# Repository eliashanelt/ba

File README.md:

# Bachelor Thesis: Enhancing the Self-Excited FluidFM Cantilever System
This is the official repo of my bachelor thesis. I will be working on improving LBB's self-excited FluidFM cantilever system
#### Where to find me?
_ETZ E 60.1_

#### Important Links
[nas setup](https://wiki.lbb.ethz.ch/it/backup)

[lbb wiki](https://people.ee.ethz.ch/~lbbwiki/doku.php?id=start)

#### How to flash fpga
open firmware/fpga/tmp/freq/freq.xpr with vivado
generate bitstream file with 'Generate Bitstream'

in firmware/fpga/tmp/freq/freq.runs/impl_1 create system_wrapper.bif containing:
all: { system_wrapper.bit }

also navigate there with the tcl shell and run
bootgen -image system_wrapper.bif -arch zynq -process_bitstream bin -o system_wrapper.bit.bin -w

after that run with the normal shell in that folder:
scp system_wrapper.bit.bin root@rp-f0bbb6.local:/root/

ssh root@rp-f0bbb6.local

password: root

on the redpitaya then run:
fpgautil - b system_wrapper.bit.bin

SCREWS M2 [smartknob] and M3 [redpitaya]

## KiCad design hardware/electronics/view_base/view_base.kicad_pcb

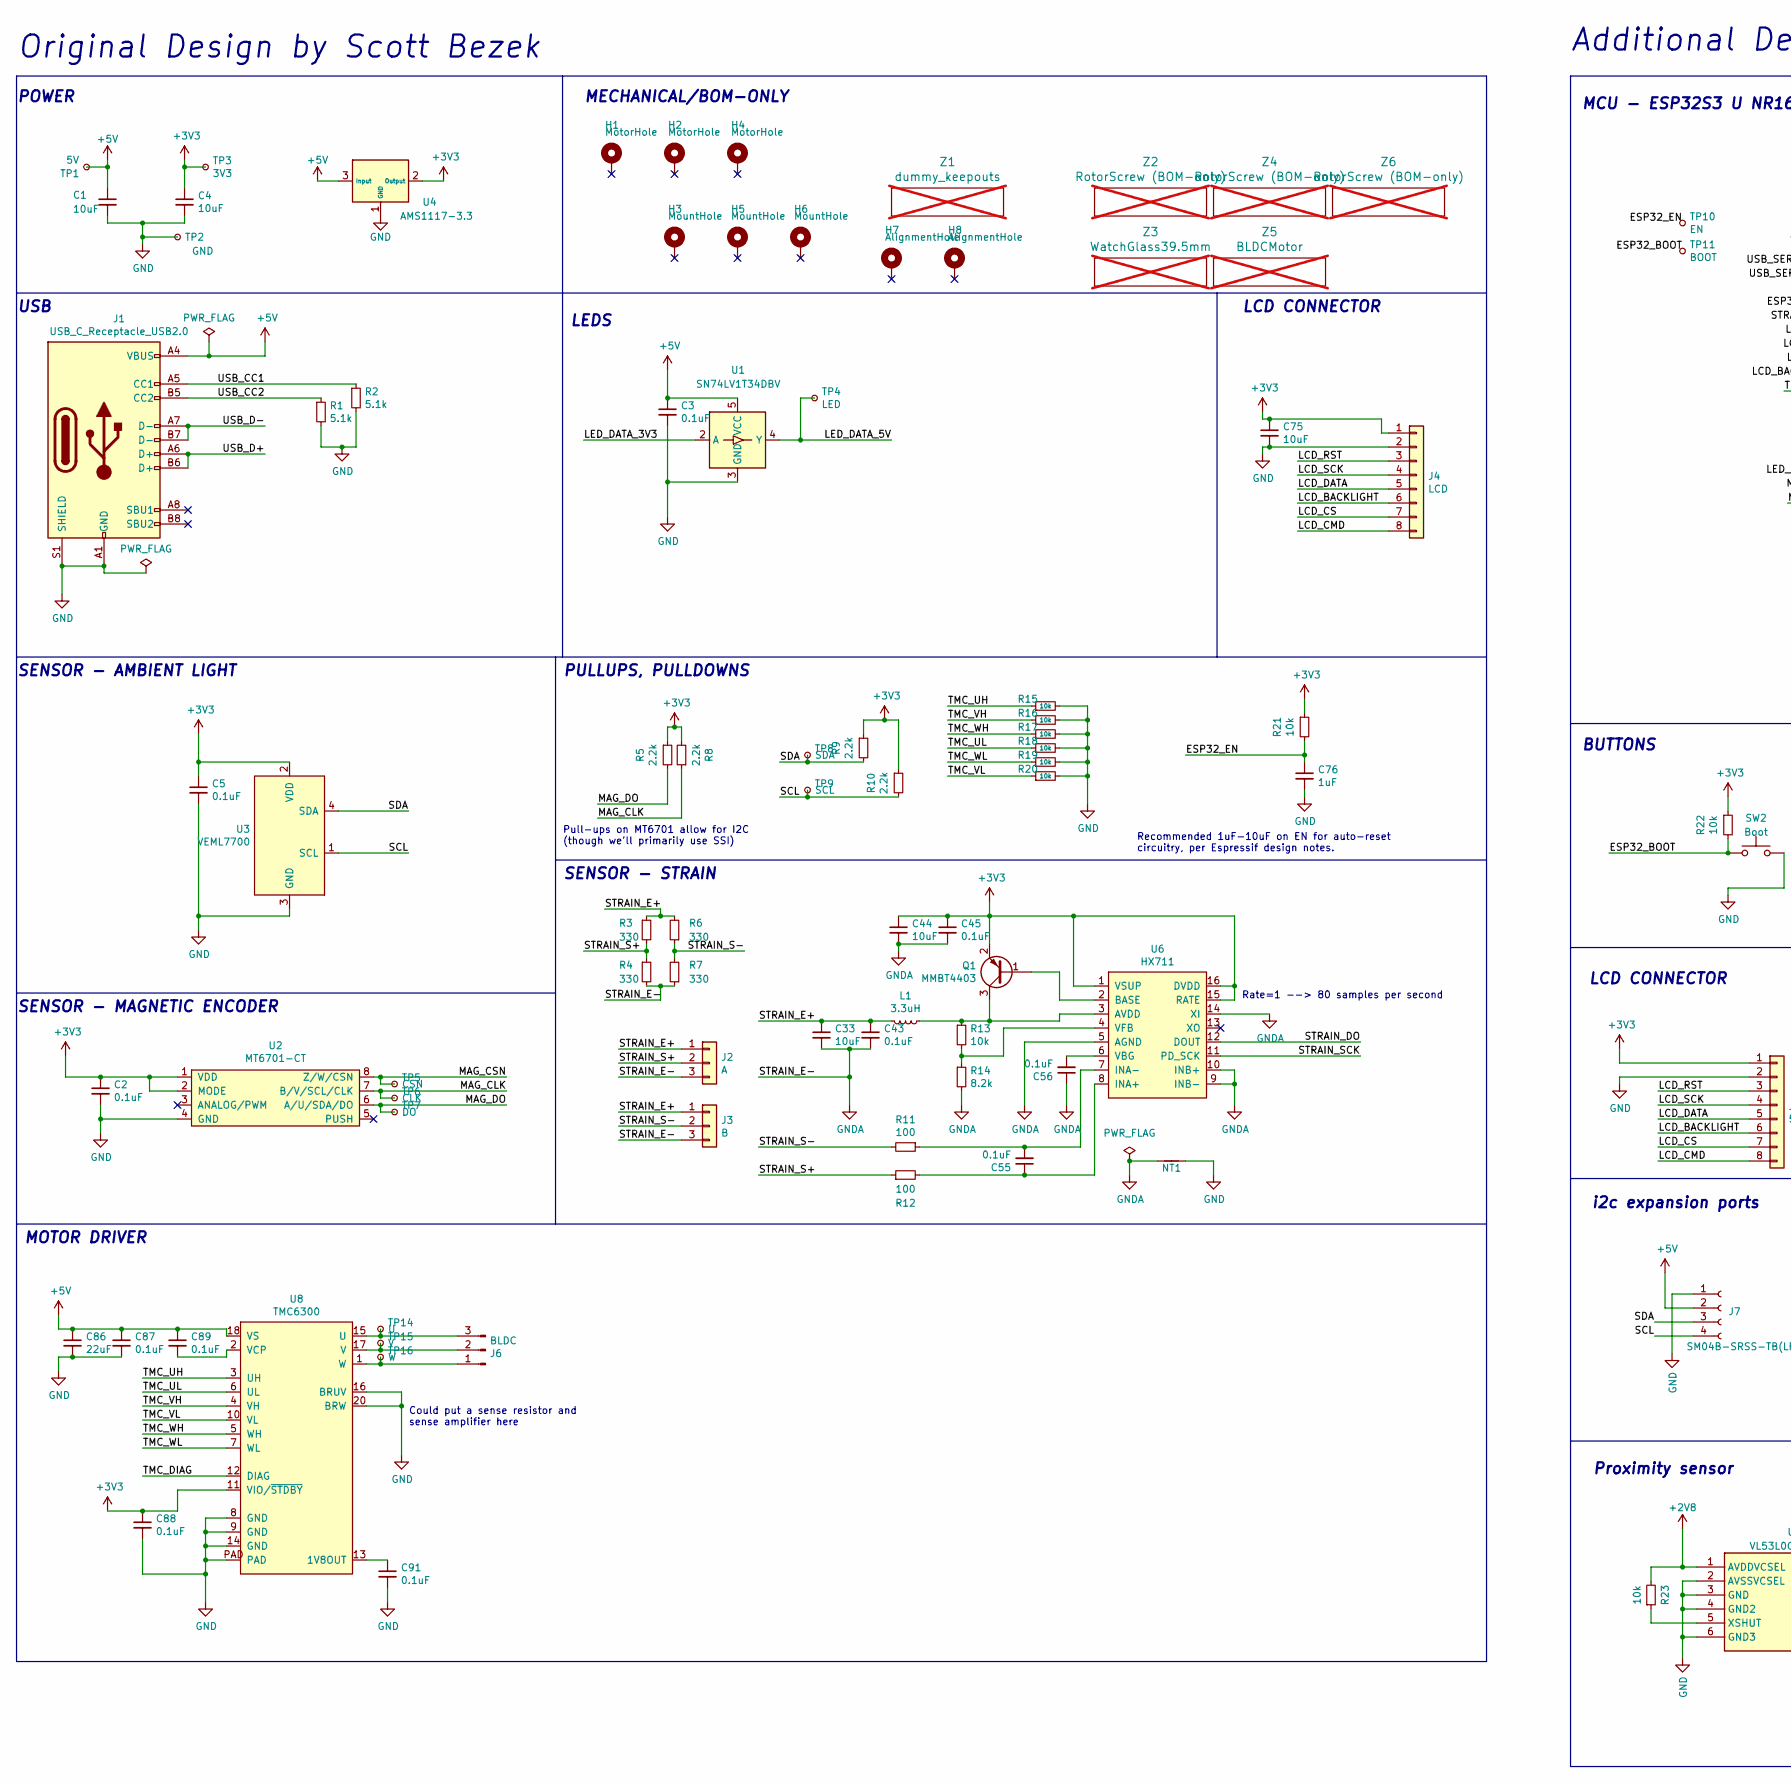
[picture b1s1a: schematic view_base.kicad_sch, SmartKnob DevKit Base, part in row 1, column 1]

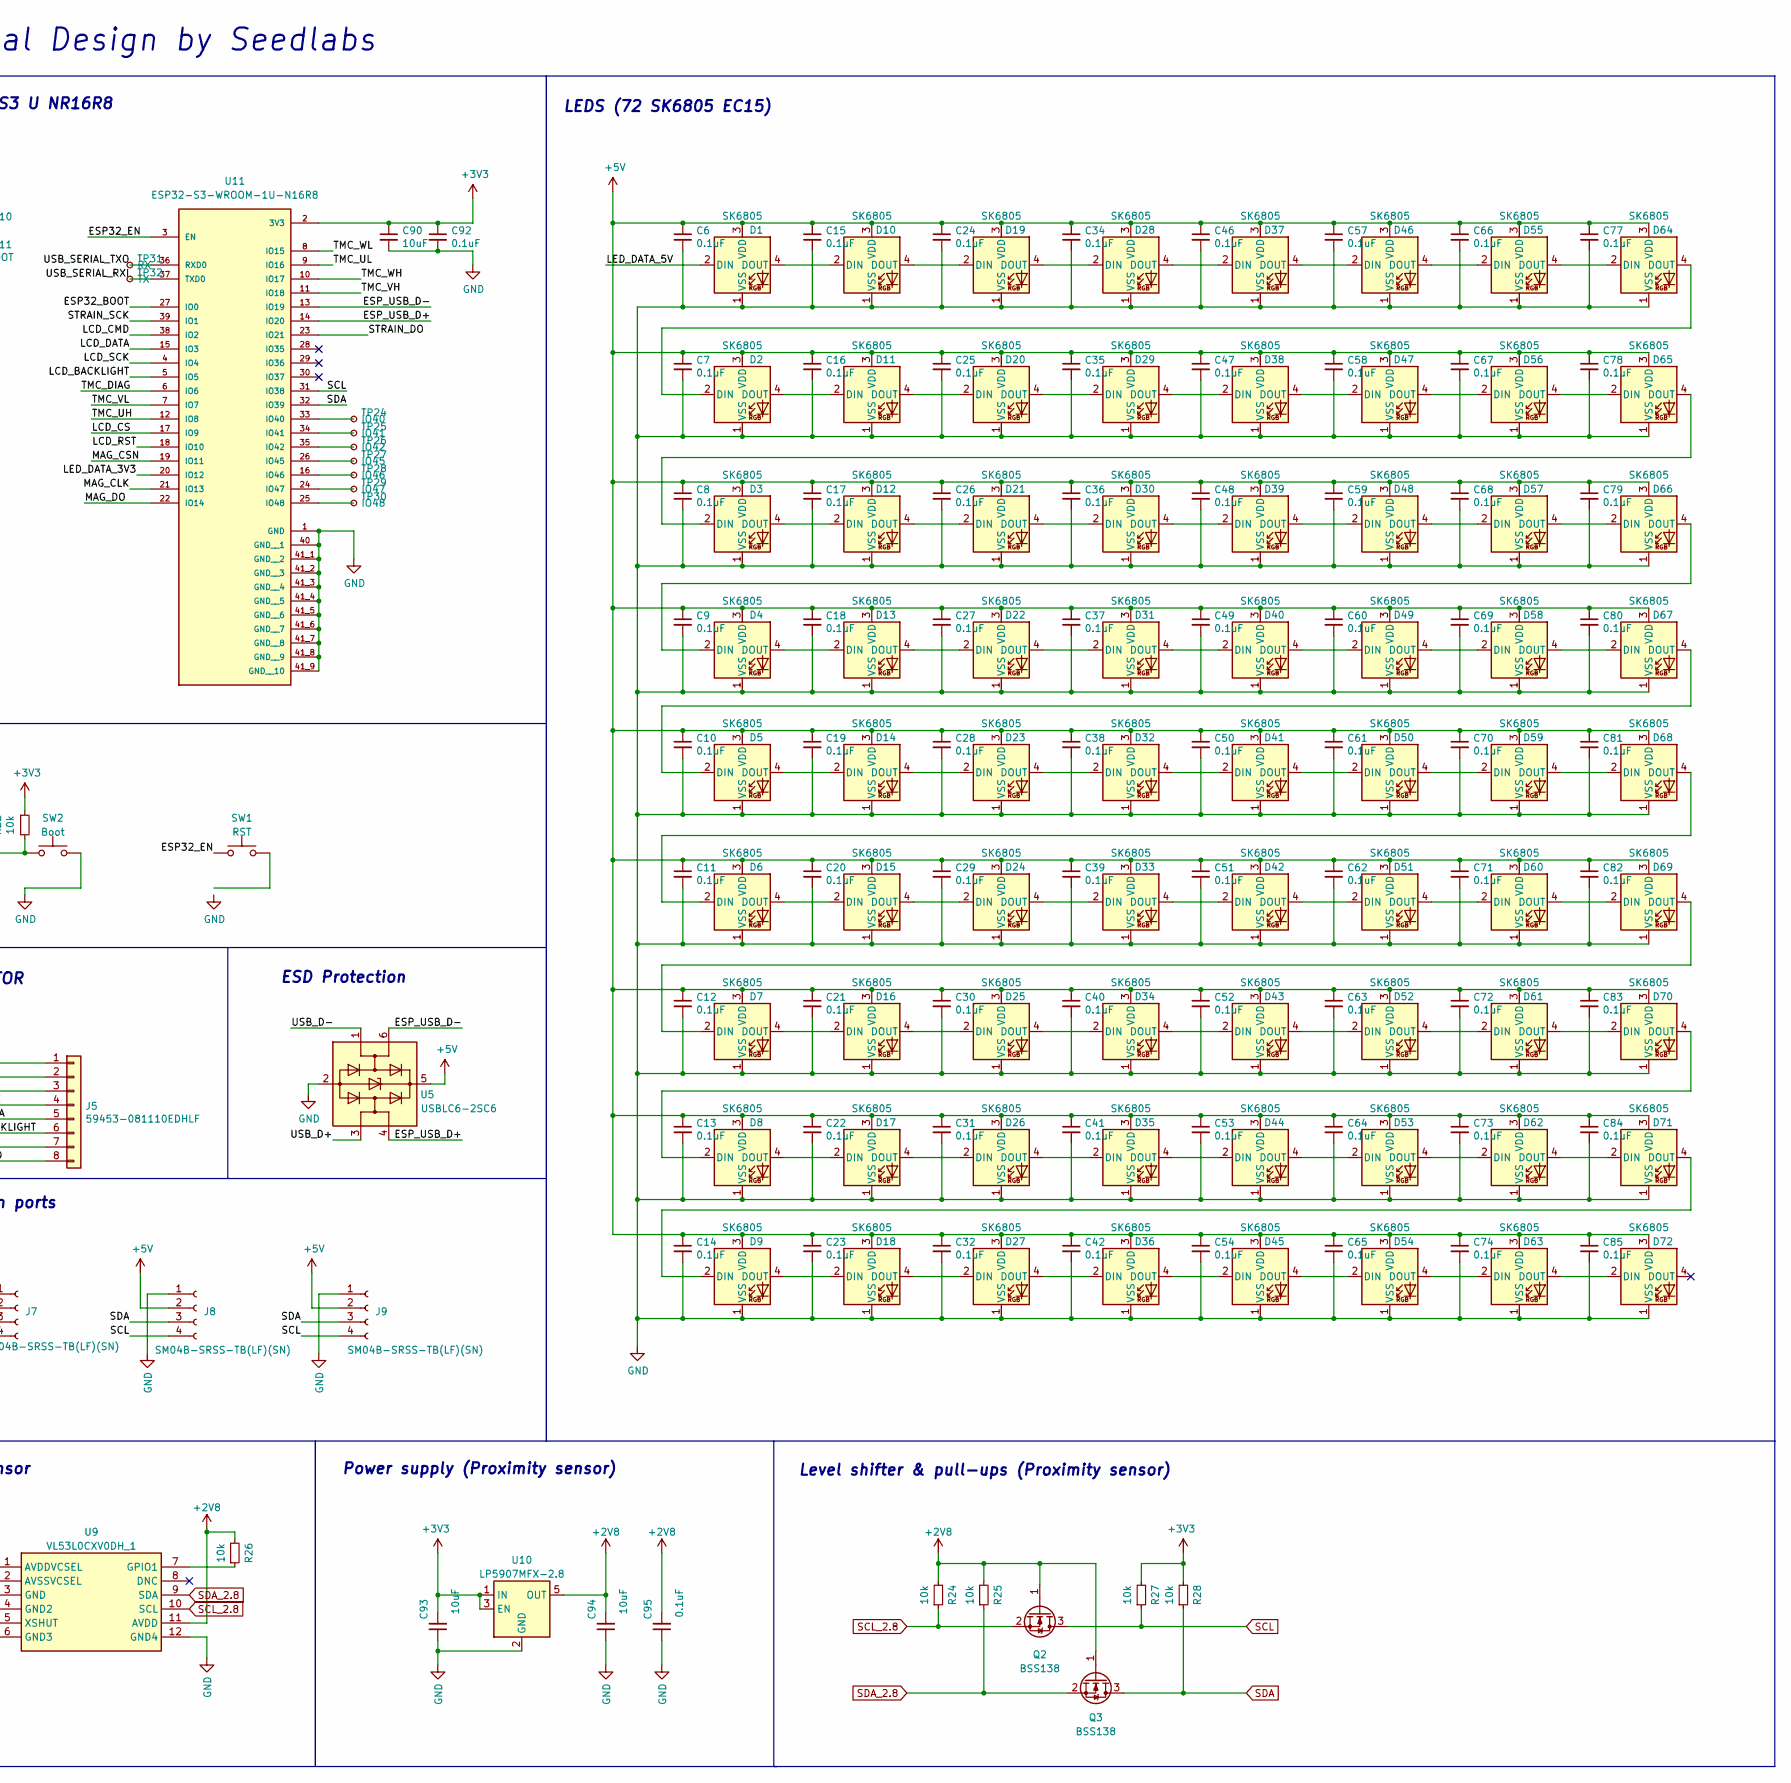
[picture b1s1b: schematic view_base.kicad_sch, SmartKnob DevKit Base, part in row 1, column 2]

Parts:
C1, C4, C33, C44, C75, C90: 10uF; C_0805_2012Metric; LCSC C15850
C2, C3, C5, C43, C45, C55, C56, C87, C88, C89, C91, C92, C95: 0.1uF; C_0603_1608Metric; LCSC C1591
C6, C7, C8, C9, C10, C11, C12, C13, C14, C15, C16, C17, C18, C19, C20, C21, C22, C23, C24, C25, C26, C27, C28, C29, C30, C31, C32, C34, C35, C36, C37, C38, C39, C40, C41, C42, C46, C47, C48, C49, C50, C51, C52, C53, C54, C57, C58, C59, C60, C61, C62, C63, C64, C65, C66, C67, C68, C69, C70, C71, C72, C73, C74, C77, C78, C79, C80, C81, C82, C83, C84, C85: 0.1uF; C_0402_1005Metric; LCSC C83056
C76: 1uF; C_0603_1608Metric; Mouser 187-CL10A105KA8NNNC
C86: 22uF; C_0805_2012Metric; LCSC C98190
C93, C94: 10uF; C_0603_1608Metric; LCSC C38898
D1, D2, D3, D4, D5, D6, D7, D8, D9, D10, D11, D12, D13, D14, D15, D16, D17, D18, D19, D20, D21, D22, D23, D24, D25, D26, D27, D28, D29, D30, D31, D32, D33, D34, D35, D36, D37, D38, D39, D40, D41, D42, D43, D44, D45, D46, D47, D48, D49, D50, D51, D52, D53, D54, D55, D56, D57, D58, D59, D60, D61, D62, D63, D64, D65, D66, D67, D68, D69, D70, D71, D72: SK6805; LED_SK6812_EC15_1.5x1.5mm; LCSC C2890035
H1, H2, H4: MotorHole; MountingHole_M1.6; LCSC C2931389
H3, H5, H6: MountHole; MountingHole_2.2mm_M2_ISO7380_Pad_NonVirtual; LCSC C2911210 or C2911532 (screw), C2961595 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
H7, H8: AlignmentHole; MountingHole_2.2mm_M2_ISO7380_Pad_NonVirtual
J1: USB_C_Receptacle_USB2.0; USB4510_NoPaste; LCSC C428463
J2: A; SolderPads_2mm_3_STRAIN
J3: B; SolderPads_2mm_3_STRAIN
J4: LCD; SolderPads_2mm_8
J5: 59453-081110EDHLF; Amphenol FCI FPC 8 pin 0.5 pitch; Mouser 649-59453081110EDHLF
J6: BLDC; 532610371; LCSC C293630
J7, J8, J9: SM04B-SRSS-TB(LF)(SN); JST_SH_SM04B-SRSS-TB_1x04-1MP_P1.00mm_Horizontal; Mouser 485-4208
L1: 3.3uH; L_0805_2012Metric; LCSC C307744
NT1: NetTie_2; NetTie-2_SMD_Pad0.5mm
Q1: MMBT4403; SOT-23; LCSC C78864
Q2, Q3: BSS138; SOT-23; LCSC C2874697
R1, R2: 5.1k; R_0603_1608Metric; LCSC C105580
R3, R4, R6, R7: 330; R_2512_6332Metric; LCSC C19866
R5, R8, R9, R10: 2.2k; R_0603_1608Metric; LCSC C4190
R11, R12: 100; R_0603_1608Metric; LCSC C319953
R13, R15, R16, R17, R18, R19, R20, R21, R22, R23, R24, R25, R26, R27, R28: 10k; R_0603_1608Metric; LCSC C98220
R14: 8.2k; R_0603_1608Metric; LCSC C114637
SW1: RST; SW_SPST_PTS810; LCSC C116501
SW2: Boot; SW_SPST_PTS810; LCSC C116501
TP1: 5V; TestPoint_Pad_D2.0mm_ValueSilk
TP2: GND; TestPoint_Pad_D2.0mm_ValueSilk
TP3: 3V3; TestPoint_Pad_D2.0mm_ValueSilk
TP4: LED; TestPoint_Pad_D2.0mm_ValueSilk
TP5: CSN; TestPoint_Pad_D2.0mm_ValueSilk
TP6: CLK; TestPoint_Pad_D2.0mm_ValueSilk
TP7: DO; TestPoint_Pad_D2.0mm_ValueSilk
TP8: SDA; TestPoint_Pad_D2.0mm_ValueSilk
TP9: SCL; TestPoint_Pad_D2.0mm_ValueSilk
TP10: EN; TestPoint_Pad_D2.0mm_ValueSilk
TP11: BOOT; TestPoint_Pad_D2.0mm_ValueSilk
TP14: U; TestPoint_Pad_D2.0mm_ValueSilk
TP15: V; TestPoint_Pad_D2.0mm_ValueSilk
TP16: W; TestPoint_Pad_D2.0mm_ValueSilk
TP24: IO40; TestPoint_Pad_D2.0mm_ValueSilk
TP25: IO41; TestPoint_Pad_D2.0mm_ValueSilk
TP26: IO42; TestPoint_Pad_D2.0mm_ValueSilk
TP27: IO45; TestPoint_Pad_D2.0mm_ValueSilk
TP28: IO46; TestPoint_Pad_D2.0mm_ValueSilk
TP29: IO47; TestPoint_Pad_D2.0mm_ValueSilk
TP30: IO48; TestPoint_Pad_D2.0mm_ValueSilk
TP31: RX; TestPoint_Pad_D2.0mm_ValueSilk
TP32: TX; TestPoint_Pad_D2.0mm_ValueSilk
U1: SN74LV1T34DBV; SOT-23-5; LCSC C100024
U2: MT6701-CT; SOIC-8_3.9x4.9mm_P1.27mm; LCSC C2856764, or C3003196
U3: VEML7700; VEML7700-TOP; Digikey VEML7700-TT
U4: AMS1117-3.3; SOT-223-3_TabPin2_GndOutIn; LCSC C6186
U5: USBLC6-2SC6; SOT-23-6; LCSC C7519
U6: HX711; SOIC-16_3.9x9.9mm_P1.27mm; LCSC C43656
U8: TMC6300; QFN-20-1EP_3x3mm_P0.4mm_EP1.65x1.65mm_ThermalVias_LargerVia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; Digikey TMC6300-LA-T
U9: VL53L0CXV0DH_1; LGA12_1; Mouser Part Number 511-VL53L0CXV0DH/1
U10: LP5907MFX-2.8; SOT-23-5; Mouser 595-LP5907MFX-2.8NPB
U11: ESP32-S3-WROOM-1U-N16R8; XCVR_ESP32-S3-WROOM-1U-N16R8; PARTREV v1.1; JLCPCB Position Offset 0,-0.5
Z1: dummy_keepouts; ViewKeepouts3d; not fitted
Z2, Z4, Z6: RotorScrew (BOM-only); bom_only_no_pin; not fitted
Z3: WatchGlass39.5mm; bom_only_no_pin; not fitted
Z5: BLDCMotor; bom_only_no_pin; not fitted

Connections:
+2V8: C94.2, C95.2, Q2.1 (G), Q3.1 (G), R23.2, R24.2, R25.2, R26.2, U9.1 (AVDDVCSEL), U9.11 (AVDD), U10.5 (OUT)
+3V3: C2.1, C4.1, C5.1, C44.1, C45.1, C75.1, C88.1, C90.1, C92.1, C93.2, J4.1, J5.1, Q1.2 (E), R5.1, R8.2, R9.1, R10.1, R21.1, R22.1, R27.2, R28.2, TP3.1, U2.1 (VDD), U2.2 (MODE), U3.2 (VDD), U4.2 (Output), U6.1 (VSUP), U6.15 (RATE), U6.16 (DVDD), U8.11 (VIO/~STDBY), U10.1 (IN), U10.3 (EN), U11.2 (3V3)
+5V: C1.1, C3.1, C6.1, C7.1, C8.1, C9.1, C10.1, C11.1, C12.1, C13.1, C14.1, C15.1, C16.1, C17.1, C18.1, C19.1, C20.1, C21.1, C22.1, C23.1, C24.1, C25.1, C26.1, C27.1, C28.1, C29.1, C30.1, C31.1, C32.1, C34.1, C35.1, C36.1, C37.1, C38.1, C39.1, C40.1, C41.1, C42.1, C46.1, C47.1, C48.1, C49.1, C50.1, C51.1, C52.1, C53.1, C54.1, C57.1, C58.1, C59.1, C60.1, C61.1, C62.1, C63.1, C64.1, C65.1, C66.1, C67.1, C68.1, C69.1, C70.1, C71.1, C72.1, C73.1, C74.1, C77.1, C78.1, C79.1, C80.1, C81.1, C82.1, C83.1, C84.1, C85.1, C86.1, C87.1, C89.1, D1.3 (VDD), D2.3 (VDD), D3.3 (VDD), D4.3 (VDD), D5.3 (VDD), D6.3 (VDD), D7.3 (VDD), D8.3 (VDD), D9.3 (VDD), D10.3 (VDD), D11.3 (VDD), D12.3 (VDD), D13.3 (VDD), D14.3 (VDD), D15.3 (VDD), D16.3 (VDD), D17.3 (VDD), D18.3 (VDD), D19.3 (VDD), D20.3 (VDD), D21.3 (VDD), D22.3 (VDD), D23.3 (VDD), D24.3 (VDD), D25.3 (VDD), D26.3 (VDD), D27.3 (VDD), D28.3 (VDD), D29.3 (VDD), D30.3 (VDD), D31.3 (VDD), D32.3 (VDD), D33.3 (VDD), D34.3 (VDD), D35.3 (VDD), D36.3 (VDD), D37.3 (VDD), D38.3 (VDD), D39.3 (VDD), D40.3 (VDD), D41.3 (VDD), D42.3 (VDD), D43.3 (VDD), D44.3 (VDD), D45.3 (VDD), D46.3 (VDD), D47.3 (VDD), D48.3 (VDD), D49.3 (VDD), D50.3 (VDD), D51.3 (VDD), D52.3 (VDD), D53.3 (VDD), D54.3 (VDD), D55.3 (VDD), D56.3 (VDD), D57.3 (VDD), D58.3 (VDD), D59.3 (VDD), D60.3 (VDD), D61.3 (VDD), D62.3 (VDD), D63.3 (VDD), D64.3 (VDD), D65.3 (VDD), D66.3 (VDD), D67.3 (VDD), D68.3 (VDD), D69.3 (VDD), D70.3 (VDD), D71.3 (VDD), D72.3 (VDD), J1.A4 (VBUS), J1.A9 (VBUS), J1.B4 (VBUS), J1.B9 (VBUS), J7.2, J8.2, J9.2, TP1.1, U1.5 (VCC), U4.3 (Input), U5.5 (VBUS), U8.18 (VS)
/ESP32_BOOT: R22.2, SW2.1, TP11.1, U11.27 (IO0)
/ESP32_EN: C76.1, R21.2, SW1.1, TP10.1, U11.3 (EN)
/ESP_USB_D+: U5.4 (I/O2), U11.14 (IO20)
/ESP_USB_D-: U5.6 (I/O1), U11.13 (IO19)
/LCD_BACKLIGHT: J4.6, J5.6, U11.5 (IO5)
/LCD_CMD: J4.8, J5.8, U11.38 (IO2)
/LCD_CS: J4.7, J5.7, U11.17 (IO9)
/LCD_DATA: J4.5, J5.5, U11.15 (IO3)
/LCD_RST: J4.3, J5.3, U11.18 (IO10)
/LCD_SCK: J4.4, J5.4, U11.4 (IO4)
/LED_DATA_3V3: U1.2 (A), U11.20 (IO12)
/LED_DATA_5V: D1.2 (DIN), TP4.1, U1.4 (Y)
/MAG_CLK: R8.1, TP6.1, U2.7 (B/V/SCL/CLK), U11.21 (IO13)
/MAG_CSN: TP5.1, U2.8 (Z/W/CSN), U11.19 (IO11)
/MAG_DO: R5.2, TP7.1, U2.6 (A/U/SDA/DO), U11.22 (IO14)
/STRAIN_DO: U6.12 (DOUT), U11.23 (IO21)
/STRAIN_E+: C33.1, C43.1, J2.1, J3.1, L1.2, R3.1, R6.2
/STRAIN_S+: J2.2, R3.2, R4.1, R12.1
/STRAIN_S-: J3.2, R6.1, R7.2, R11.2
/STRAIN_SCK: U6.11 (PD_SCK), U11.39 (IO1)
/TMC_DIAG: U8.12 (DIAG), U11.6 (IO6)
/TMC_UH: R15.1, U8.3 (UH), U11.12 (IO8)
/TMC_UL: R18.1, U8.6 (UL), U11.9 (IO16)
/TMC_VH: R16.1, U8.4 (VH), U11.11 (IO18)
/TMC_VL: R20.1, U8.10 (VL), U11.7 (IO7)
/TMC_WH: R17.1, U8.5 (WH), U11.10 (IO17)
/TMC_WL: R19.1, U8.7 (WL), U11.8 (IO15)
/USB_CC1: J1.A5 (CC1), R2.1
/USB_CC2: J1.B5 (CC2), R1.1
/USB_D+: J1.A6 (D+), J1.B6 (D+), U5.3 (I/O2)
/USB_D-: J1.A7 (D-), J1.B7 (D-), U5.1 (I/O1)
/USB_SERIAL_RXI: TP32.1, U11.37 (TXD0); also elsewhere on the board
/USB_SERIAL_TXO: TP31.1, U11.36 (RXD0); also elsewhere on the board
GND: C1.2, C2.2, C3.2, C4.2, C5.2, C6.2, C7.2, C8.2, C9.2, C10.2, C11.2, C12.2, C13.2, C14.2, C15.2, C16.2, C17.2, C18.2, C19.2, C20.2, C21.2, C22.2, C23.2, C24.2, C25.2, C26.2, C27.2, C28.2, C29.2, C30.2, C31.2, C32.2, C34.2, C35.2, C36.2, C37.2, C38.2, C39.2, C40.2, C41.2, C42.2, C46.2, C47.2, C48.2, C49.2, C50.2, C51.2, C52.2, C53.2, C54.2, C57.2, C58.2, C59.2, C60.2, C61.2, C62.2, C63.2, C64.2, C65.2, C66.2, C67.2, C68.2, C69.2, C70.2, C71.2, C72.2, C73.2, C74.2, C75.2, C76.2, C77.2, C78.2, C79.2, C80.2, C81.2, C82.2, C83.2, C84.2, C85.2, C86.2, C87.2, C88.2, C90.2, C91.2, C92.2, C93.1, C94.1, C95.1, D1.1 (VSS), D2.1 (VSS), D3.1 (VSS), D4.1 (VSS), D5.1 (VSS), D6.1 (VSS), D7.1 (VSS), D8.1 (VSS), D9.1 (VSS), D10.1 (VSS), D11.1 (VSS), D12.1 (VSS), D13.1 (VSS), D14.1 (VSS), D15.1 (VSS), D16.1 (VSS), D17.1 (VSS), D18.1 (VSS), D19.1 (VSS), D20.1 (VSS), D21.1 (VSS), D22.1 (VSS), D23.1 (VSS), D24.1 (VSS), D25.1 (VSS), D26.1 (VSS), D27.1 (VSS), D28.1 (VSS), D29.1 (VSS), D30.1 (VSS), D31.1 (VSS), D32.1 (VSS), D33.1 (VSS), D34.1 (VSS), D35.1 (VSS), D36.1 (VSS), D37.1 (VSS), D38.1 (VSS), D39.1 (VSS), D40.1 (VSS), D41.1 (VSS), D42.1 (VSS), D43.1 (VSS), D44.1 (VSS), D45.1 (VSS), D46.1 (VSS), D47.1 (VSS), D48.1 (VSS), D49.1 (VSS), D50.1 (VSS), D51.1 (VSS), D52.1 (VSS), D53.1 (VSS), D54.1 (VSS), D55.1 (VSS), D56.1 (VSS), D57.1 (VSS), D58.1 (VSS), D59.1 (VSS), D60.1 (VSS), D61.1 (VSS), D62.1 (VSS), D63.1 (VSS), D64.1 (VSS), D65.1 (VSS), D66.1 (VSS), D67.1 (VSS), D68.1 (VSS), D69.1 (VSS), D70.1 (VSS), D71.1 (VSS), D72.1 (VSS), J1.A1 (GND), J1.A12 (GND), J1.B1 (GND), J1.B12 (GND), J1.S1 (SHIELD), J4.2, J5.2, J7.1, J8.1, J9.1, NT1.2, R1.2, R2.2, R15.2, R16.2, R17.2, R18.2, R19.2, R20.2, SW1.2, SW2.2, TP2.1, U1.3 (GND), U2.4 (GND), U3.3 (GND), U4.1 (GND), U5.2 (GND), U8.8 (GND), U8.9 (GND), U8.14 (GND), U8.16 (BRUV), U8.20 (BRW), U8.PAD, U9.2 (AVSSVCSEL), U9.3 (GND), U9.4 (GND2), U9.6 (GND3), U9.12 (GND4), U10.2 (GND), U11.1 (GND), U11.40 (GND__1), U11.41_1 (GND__2), U11.41_2 (GND__3), U11.41_3 (GND__4), U11.41_4 (GND__5), U11.41_5 (GND__6), U11.41_6 (GND__7), U11.41_7 (GND__8), U11.41_8 (GND__9), U11.41_9 (GND__10)
GNDA: C33.2, C43.2, C44.2, C45.2, C56.1, J2.3, J3.3, NT1.1, R4.2, R7.1, R14.2, U6.5 (AGND), U6.9 (INB-), U6.10 (INB+), U6.14 (XI)
unnamed: D1.4 (DOUT), D10.2 (DIN)
unnamed: D2.2 (DIN), D64.4 (DOUT)
unnamed: D3.2 (DIN), D65.4 (DOUT)
unnamed: D4.2 (DIN), D66.4 (DOUT)
unnamed: D5.2 (DIN), D67.4 (DOUT)
unnamed: D6.2 (DIN), D68.4 (DOUT)
unnamed: D10.4 (DOUT), D19.2 (DIN)
unnamed: D2.4 (DOUT), D11.2 (DIN)
unnamed: D11.4 (DOUT), D20.2 (DIN)
unnamed: D3.4 (DOUT), D12.2 (DIN)
unnamed: D12.4 (DOUT), D21.2 (DIN)
unnamed: D4.4 (DOUT), D13.2 (DIN)
unnamed: D13.4 (DOUT), D22.2 (DIN)
unnamed: D5.4 (DOUT), D14.2 (DIN)
unnamed: D14.4 (DOUT), D23.2 (DIN)
unnamed: D6.4 (DOUT), D15.2 (DIN)
unnamed: D15.4 (DOUT), D24.2 (DIN)
unnamed: D7.4 (DOUT), D16.2 (DIN)
unnamed: D16.4 (DOUT), D25.2 (DIN)
unnamed: D8.4 (DOUT), D17.2 (DIN)
unnamed: D17.4 (DOUT), D26.2 (DIN)
unnamed: D9.4 (DOUT), D18.2 (DIN)
unnamed: D18.4 (DOUT), D27.2 (DIN)
unnamed: D19.4 (DOUT), D28.2 (DIN)
unnamed: D20.4 (DOUT), D29.2 (DIN)
unnamed: D21.4 (DOUT), D30.2 (DIN)
unnamed: D22.4 (DOUT), D31.2 (DIN)
unnamed: D23.4 (DOUT), D32.2 (DIN)
unnamed: D24.4 (DOUT), D33.2 (DIN)
unnamed: D25.4 (DOUT), D34.2 (DIN)
unnamed: D26.4 (DOUT), D35.2 (DIN)
unnamed: D27.4 (DOUT), D36.2 (DIN)
unnamed: D28.4 (DOUT), D37.2 (DIN)
unnamed: D29.4 (DOUT), D38.2 (DIN)
unnamed: D30.4 (DOUT), D39.2 (DIN)
unnamed: D31.4 (DOUT), D40.2 (DIN)
unnamed: D32.4 (DOUT), D41.2 (DIN)
unnamed: D33.4 (DOUT), D42.2 (DIN)
unnamed: D34.4 (DOUT), D43.2 (DIN)
unnamed: D35.4 (DOUT), D44.2 (DIN)
unnamed: D36.4 (DOUT), D45.2 (DIN)
unnamed: D37.4 (DOUT), D46.2 (DIN)
unnamed: D38.4 (DOUT), D47.2 (DIN)
unnamed: D39.4 (DOUT), D48.2 (DIN)
unnamed: D40.4 (DOUT), D49.2 (DIN)
unnamed: D41.4 (DOUT), D50.2 (DIN)
unnamed: D42.4 (DOUT), D51.2 (DIN)
unnamed: D43.4 (DOUT), D52.2 (DIN)
unnamed: D44.4 (DOUT), D53.2 (DIN)
unnamed: D45.4 (DOUT), D54.2 (DIN)
unnamed: D46.4 (DOUT), D55.2 (DIN)
unnamed: D47.4 (DOUT), D56.2 (DIN)
unnamed: D48.4 (DOUT), D57.2 (DIN)
unnamed: D49.4 (DOUT), D58.2 (DIN)
unnamed: D50.4 (DOUT), D59.2 (DIN)
unnamed: D51.4 (DOUT), D60.2 (DIN)
unnamed: D52.4 (DOUT), D61.2 (DIN)
unnamed: D53.4 (DOUT), D62.2 (DIN)
unnamed: D54.4 (DOUT), D63.2 (DIN)
unnamed: D55.4 (DOUT), D64.2 (DIN)
unnamed: D56.4 (DOUT), D65.2 (DIN)
unnamed: D57.4 (DOUT), D66.2 (DIN)
unnamed: D58.4 (DOUT), D67.2 (DIN)
unnamed: D59.4 (DOUT), D68.2 (DIN)
unnamed: D60.4 (DOUT), D69.2 (DIN)
unnamed: D61.4 (DOUT), D70.2 (DIN)
unnamed: D62.4 (DOUT), D71.2 (DIN)
unnamed: D63.4 (DOUT), D72.2 (DIN)
unnamed: D7.2 (DIN), D69.4 (DOUT)
unnamed: D8.2 (DIN), D70.4 (DOUT)
unnamed: D9.2 (DIN), D71.4 (DOUT)
unnamed: J6.1, TP16.1, U8.1 (W)
unnamed: J6.2, TP15.1, U8.17 (V)
unnamed: J6.3, TP14.1, U8.15 (U)
unnamed: Q1.1 (B), U6.2 (BASE)
unnamed: L1.1, Q1.3 (C), R13.1, U6.3 (AVDD)
unnamed: C55.1, R12.2, U6.8 (INA+)
unnamed: C55.2, R11.1, U6.7 (INA-)
unnamed: C56.2, U6.6 (VBG)
unnamed: R13.2, R14.1, U6.4 (VFB)
unnamed: C91.1, U8.13 (1V8OUT)
unnamed: C89.2, U8.2 (VCP)
unnamed: R26.1, U9.7 (GPIO1)
unnamed: R23.1, U9.5 (XSHUT)
unnamed: TP24.1, U11.33 (IO40)
unnamed: TP25.1, U11.34 (IO41)
unnamed: TP26.1, U11.35 (IO42)
unnamed: TP27.1, U11.26 (IO45)
unnamed: TP28.1, U11.16 (IO46)
unnamed: TP29.1, U11.24 (IO47)
unnamed: TP30.1, U11.25 (IO48)
SCL: J7.4, J8.4, J9.4, Q2.3 (D), R10.2, R27.1, TP9.1, U3.1 (SCL), U11.31 (IO38)
SCL_2.8: Q2.2 (S), R24.1, U9.10 (SCL)
SDA: J7.3, J8.3, J9.3, Q3.3 (D), R9.2, R28.1, TP8.1, U3.4 (SDA), U11.32 (IO39)
SDA_2.8: Q3.2 (S), R25.1, U9.9 (SDA)

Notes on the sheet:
POWER
Could put a sense resistor and sense amplifier here
MCU - ESP32S3 U NR16R8
SENSOR - MAGNETIC ENCODER
MOTOR DRIVER
MECHANICAL/BOM-ONLY
Pull-ups on MT6701 allow for I2C (though we'll primarily use SSI)
Rate=1 --> 80 samples per second
Additional Design by Seedlabs
Proximity sensor
SENSOR - AMBIENT LIGHT
Power supply (Proximity sensor)
Original Design by Scott Bezek
Recommended 1uF-10uF on EN for auto-reset circuitry, per Espressif design notes.
USB
SENSOR - STRAIN
LEDS
LEDS (72 SK6805 EC15)
BUTTONS
PULLUPS, PULLDOWNS
LCD CONNECTOR
i2c expansion ports
ESD Protection
Level shifter & pull-ups (Proximity sensor)

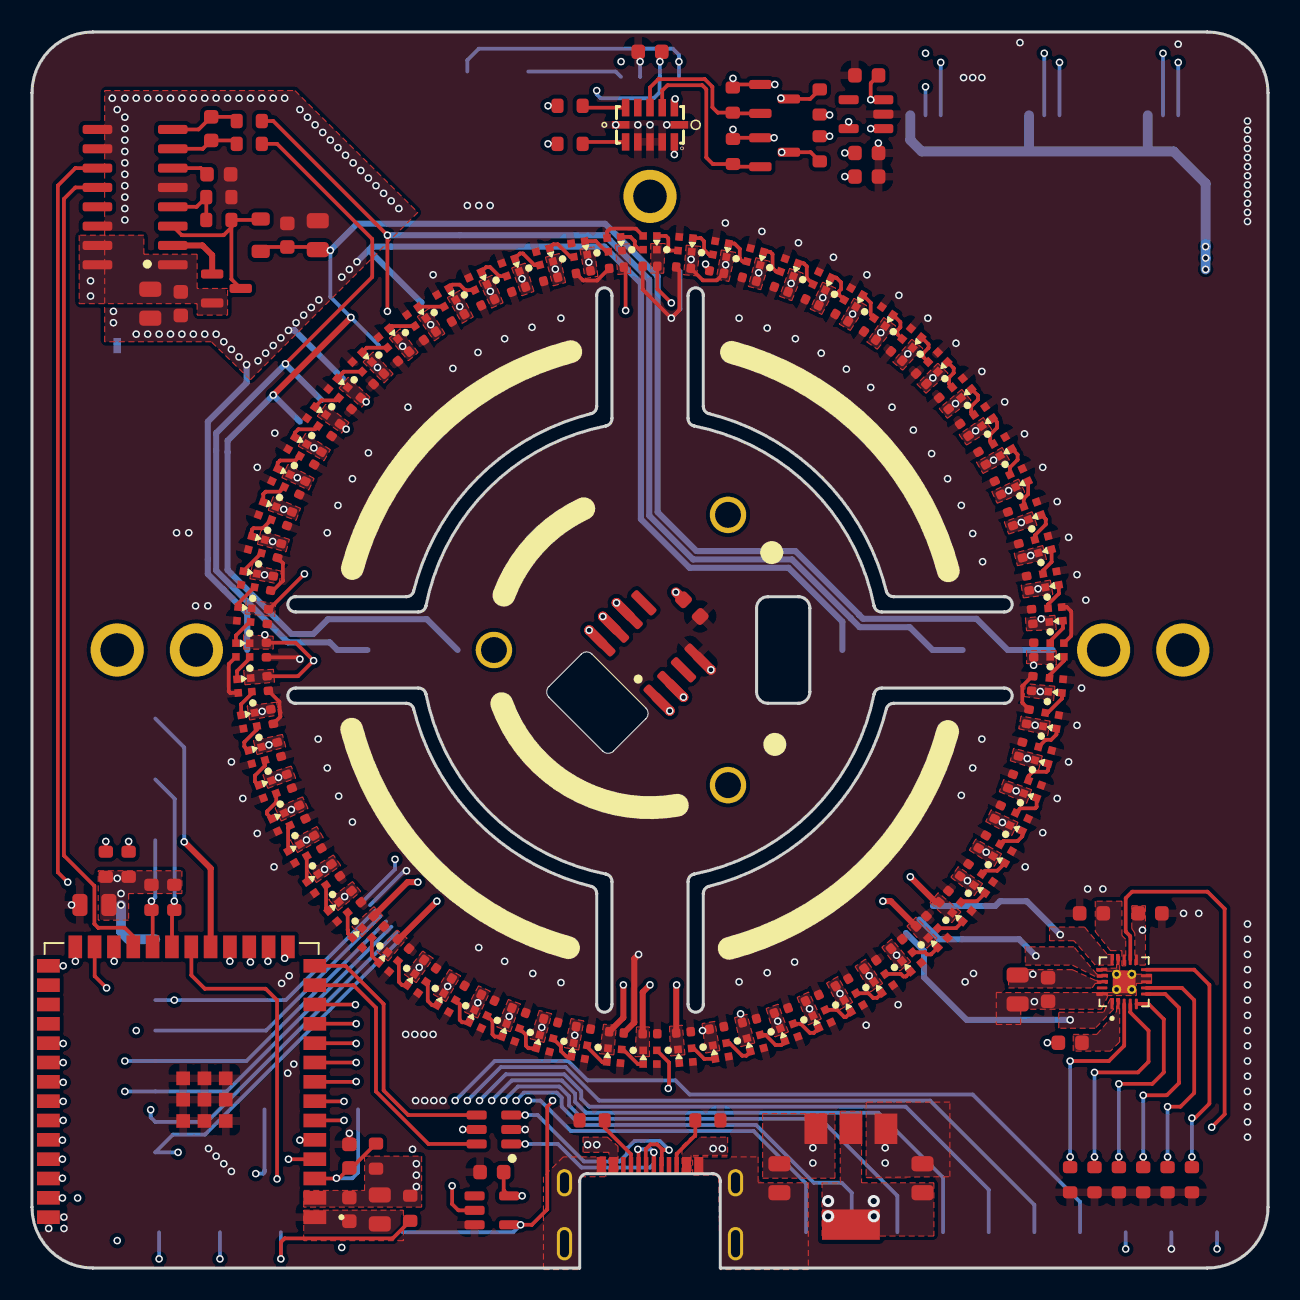
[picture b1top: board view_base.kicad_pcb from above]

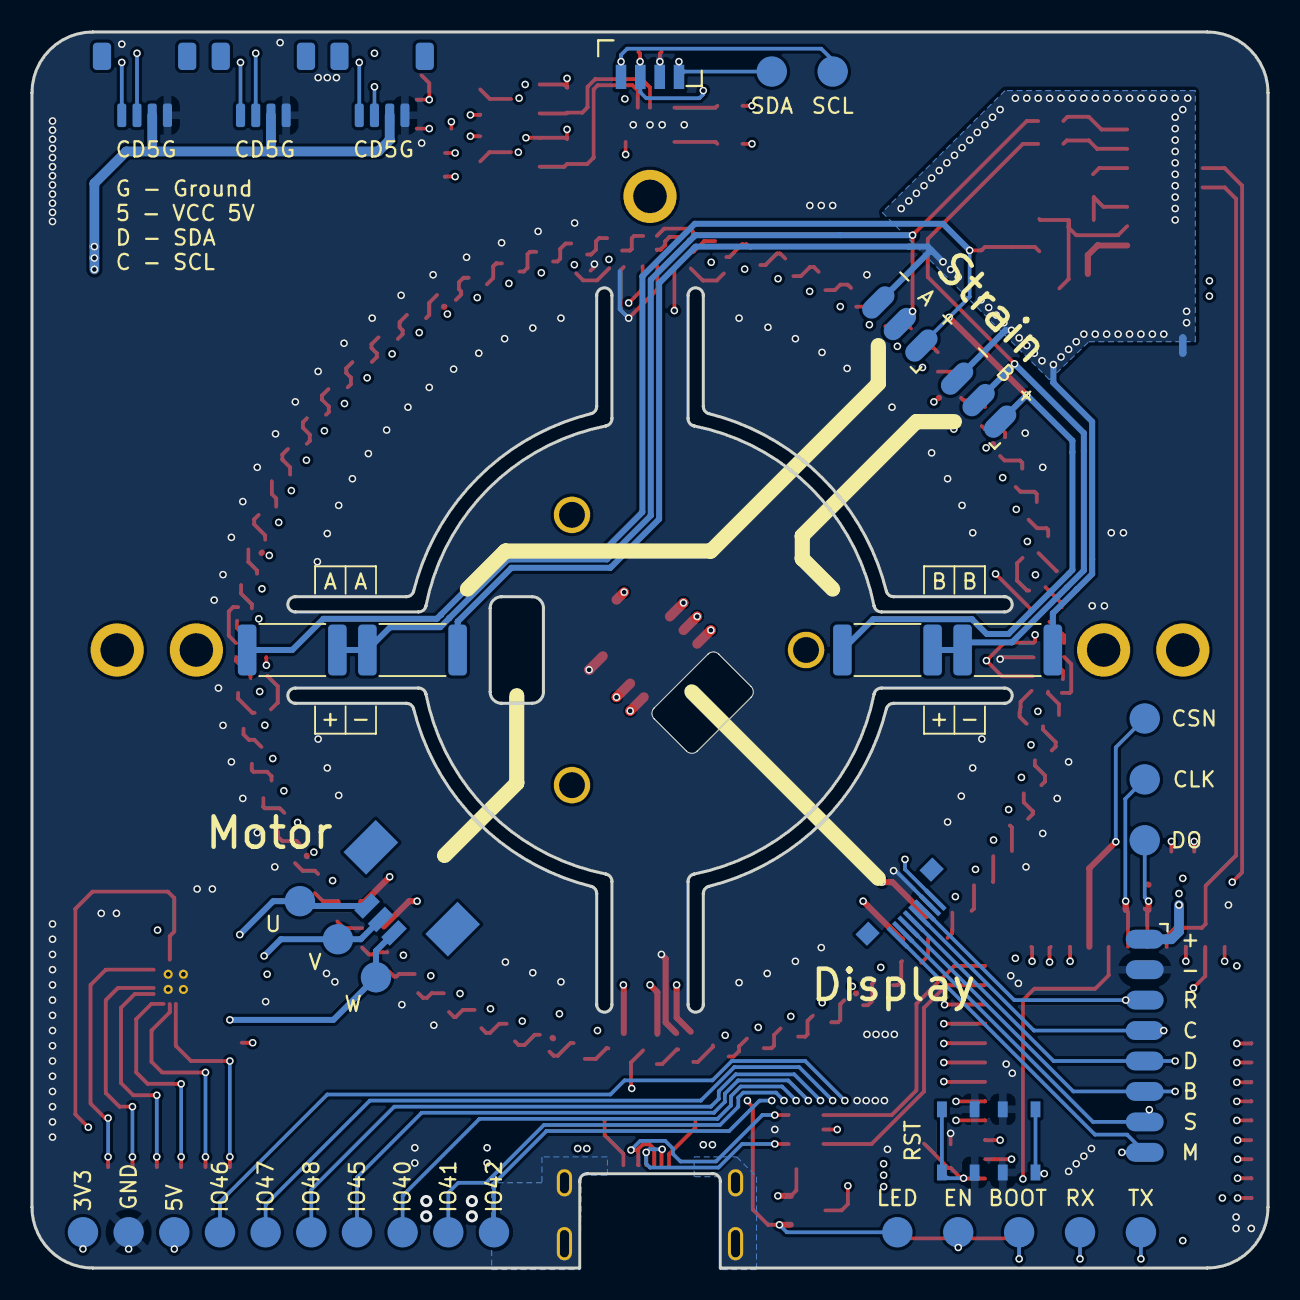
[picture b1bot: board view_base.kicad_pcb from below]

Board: 4 copper layers, 81.2 x 81.2 mm, 257 parts (39 on the bottom side), 126 nets.

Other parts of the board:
TP12: RX; TestPoint_Pad_D2.0mm_ValueSilk
TP13: TX; TestPoint_Pad_D2.0mm_ValueSilk
TP17: IO40; TestPoint_Pad_D2.0mm_ValueSilk
TP18: IO41; TestPoint_Pad_D2.0mm_ValueSilk
TP19: IO42; TestPoint_Pad_D2.0mm_ValueSilk
TP20: IO45; TestPoint_Pad_D2.0mm_ValueSilk
TP21: IO46; TestPoint_Pad_D2.0mm_ValueSilk
TP22: IO47; TestPoint_Pad_D2.0mm_ValueSilk
TP23: IO48; TestPoint_Pad_D2.0mm_ValueSilk

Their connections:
/USB_SERIAL_RXI: TP13.1; also elsewhere on the board
/USB_SERIAL_TXO: TP12.1; also elsewhere on the board

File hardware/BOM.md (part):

Current BOM export
Screen BOM

|Id |Designator|Footprint                       |Quantity|Designation               |Supplier and ref|FIELD7|FIELD8|
|---|----------|--------------------------------|--------|--------------------------|----------------|------|------|
|1  |REF**     |fpc_wire_hole_6mm_extended      |1       |fpc_wire_hole_6mm_extended|                |      |      |
|2  |Q1        |SOT-23                          |1       |2N7002                    |                |      |      |
|3  |R1        |R_0603_1608Metric               |1       |10k                       |                |      |      |
|4  |R2        |R_0603_1608Metric               |1       |22R                       |                |      |      |
|5  |R3        |R_0603_1608Metric               |1       |1M                        |                |      |      |
|6  |C2        |C_0603_1608Metric               |1       |0.1uF                     |                |      |      |
|7  |C1        |C_0603_1608Metric               |1       |22uF                      |                |      |      |
|8  |J6        |Amphenol FCI FPC 8 pin 0.5 pitch|1       |LCD - FPC                 |                |      |      |

Base BOM
|Id |Designator                                                                                                                                                                                                                                                                                 |Footprint                                                       |Quantity|Designation            |Supplier and ref|FIELD7|FIELD8|
|---|-------------------------------------------------------------------------------------------------------------------------------------------------------------------------------------------------------------------------------------------------------------------------------------------|----------------------------------------------------------------|--------|-----------------------|----------------|------|------|
|1  |J1                                                                                                                                                                                                                                                                                         |USB4510_NoPaste                                                 |1       |USB_C_Receptacle_USB2.0|                |      |      |
|2  |R2,R1                                                                                                                                                                                                                                                                                      |R_0603_1608Metric                                               |2       |5.1k                   |                |      |      |
|3  |C86                                                                                                                                                                                                                                                                                        |C_0805_2012Metric                                               |1       |22uF                   |                |      |      |
|4  |C87,C89,C88,C56,C45,C5,C91,C43,C55,C92                                                                                                                                                                                                                                                     |C_0603_1608Metric                                               |10      |0.1uF                  |                |      |      |
|5  |C44,C33,C75,C4,C1,C90                                                                                                                                                                                                                                                                      |C_0805_2012Metric                                               |6       |10uF                   |                |      |      |
|6  |Q1                                                                                                                                                                                                                                                                                         |SOT-23                                                          |1       |MMBT4403               |                |      |      |
|7  |R14                                                                                                                                                                                                                                                                                        |R_0603_1608Metric                                               |1       |8.2k                   |                |      |      |
|8  |R11,R12                                                                                                                                                                                                                                                                                    |R_0603_1608Metric                                               |2       |100                    |                |      |      |
|9  |U1                                                                                                                                                                                                                                                                                         |SOT-23-5                                                        |1       |SN74LV1T34DBV          |                |      |      |
|10 |L1                                                                                                                                                                                                                                                                                         |L_0805_2012Metric                                               |1       |3.3uH                  |                |      |      |
|11 |U8                                                                                                                                                                                                                                                                                         |QFN-20-1EP_3x3mm_P0.4mm_EP1.65x1.65mm_ThermalVias_LargerViaHoles|1       |TMC6300                |                |      |      |
|12 |R8,R5,R10,R9                                                                                                                                                                                                                                                                               |R_0603_1608Metric                                               |4       |2.2k                   |                |      |      |
|13 |U2                                                                                                                                                                                                                                                                                         |SOIC-8_3.9x4.9mm_P1.27mm                                        |1       |MT6701-CT              |                |      |      |
|14 |C2,C3                                                                                                                                                                                                                                                                                      |C_0603_1608Metric                                               |2       |0.1uF                  |                |      |      |
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

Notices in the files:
parts and their libraries:
Copyright 2021 Accelerated Designs. All rights reserved.
